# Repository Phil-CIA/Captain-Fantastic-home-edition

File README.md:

# Captain Fantastic – Home Edition

Firmware and hardware files for a restored Captain Fantastic pinball machine running on ESP32.

## Repository Layout

| Path | Description |
|------|-------------|
| `src/` `include/` `data/` | **Legacy firmware** – working single-board ESP32 firmware with External Flash OTA |
| `Captain-v2/` | **Captain v2 firmware** – clean split-MPU architecture (control + matrix boards) |
| `hardware/` | KiCad schematics, gerbers, and board-design backups |
| `docs/` | Project documentation, setup guides, and handoff notes |
| `archive/` | Historical backups, experiments, and recovery copies |
| `music/` | Test audio files used with the music streaming server |

## PlatformIO Projects

This repo contains **multiple PlatformIO projects**:

### 1. Legacy Firmware (root)
- `platformio.ini` at the repository root
- Active environment: `combined_rtos`
- Targets a single ESP32 running gameplay, displays, sound, and OTA

### 2. Captain v2 shared source tree
- `Captain-v2/platformio.ini`
- Shared build definitions and source for split-MPU firmware
- Includes environments for control, matrix, and display-link variants
- Shared source only; not the current matrix bring-up source of truth
- Separates control logic and switch/lamp matrix scanning across two ESP32 boards

### 3. Captain v2 board-specific projects
- `Captain-v2-control/platformio.ini` (control board focused project)
- `Captain-v2-matrix/platformio.ini` (matrix board focused project)
- Both reference shared source under `Captain-v2/` and keep board workflows isolated
- Current active board workflows:
	- Matrix board: `Captain-v2-matrix`, env `captain_matrix_idf`, COM4
	- Control board: `Captain-v2`, env `captain_control`, COM5

> **VS Code tip:** Open the specific project folder you are actively working on (`Captain-v2-control/` or `Captain-v2-matrix/`) so tasks and upload settings stay board-specific.

## Current Development Focus

- Active matrix bring-up/runtime source of truth is `Captain-v2-matrix/src/matrix_app_main.cpp`
- Matrix MCU appears on I2C as a register-based peripheral at `0x24` (HT16K33-style model)
- Matrix/control communication path is now usable for gameplay bring-up:
	- control-side polarity normalization and stability filtering restored usable switch behavior
	- repeated held-switch scoring was fixed
	- gameplay-side bumper / slingshot output mapping has been corrected
- Matrix protocol details and test workflow are documented in:
	- `Captain-v2-matrix/README.md`
- Remaining open issue is residual lamp flicker, but the structured blink component was traced to matrix-side periodic debug / housekeeping work in the refresh loop
- Current stop-point is good enough to continue gameplay bring-up while leaving a later focused flicker cleanup pass
- Hardware iteration note (March 2026): reduce the high-side rail voltage first to improve BSS84/BSS138 gate-drive margin before pursuing transistor substitutions (documented in `Captain-v2-matrix/README.md`, section 11)
- Redesign parking lot for next board iteration: `docs/NEXT_ITERATION_RECOMMENDATIONS.md`

## Music Streaming Server

`music_server.py` / `Start-MusicServer.ps1` stream audio to the pinball machine over Wi-Fi. See `docs/MP3_MUSIC_SETUP.md` and `docs/WIFI_STREAMING_SETUP.md` for setup.

## Documentation

All setup guides and reference docs are in `docs/`. See `docs/REPO_INDEX.md` for a full index.

## KiCad Current Project Entry Points

If KiCad is opening the wrong local copy, use only these repo project files:

- `hardware/kicad/captain_matrix/Pinball matrix board.kicad_pro`
- `hardware/kicad/captain_control/Pinball Control board.kicad_pro`
- `hardware/kicad/legacy/Hat board.kicad_pro` (historical reference project)

To keep KiCad focused on repo paths:

1. Launch with `Open-KiCad.ps1` from repo root.
2. Run `Reset-KiCad-Recents-ToRepo.ps1` once to clear stale KiCad recent/open project paths.
3. Use `hardware/kicad/SOURCE_OF_TRUTH.md` as the canonical board-path map.

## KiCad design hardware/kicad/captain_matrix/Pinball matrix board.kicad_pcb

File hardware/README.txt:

This folder contains hardware design files, schematics, PCB layouts, and fabrication exports for Captain Fantastic v2.

Canonical project map and opening policy:
- kicad/SOURCE_OF_TRUTH.md

## Current Active Designs (v2 split-MPU architecture)

Structure:
- kicad/captain_control/: Main control board (ESP32 DevKit) — gameplay, audio, solenoids, headbox lamps, OTA
- kicad/captain_matrix/: Switch/lamp matrix board (ESP32 DevKit) — playfield matrix scanning, I2C slave
- kicad/7seg_display/: Standalone 7-segment display board (I2C HT16K33, 6-digit)

## Project support files
- kicad/libs/: project symbol/footprint libraries and KiCad tables

## Historical / Legacy
- kicad/legacy/: Hat board (superseded single-board v1 design — trace size and SR enable fixed in v2 split)
- kicad/esp32vroom/: Original ESP32Vroom KiCad project files (historical reference)

Important:
- Open active projects only from kicad/captain_control and kicad/captain_matrix.
- Treat kicad/legacy, kicad/esp32vroom, and archive/ as read-only historical sources.

## Fabrication archives
- gerbers/root-export-esp32vroom/: root-level export set moved from repo root
- gerbers/legacy-gerber-files/: older export set moved from "Gerber files"
- backups/esp32vroom-backups/: historical zipped hardware backups

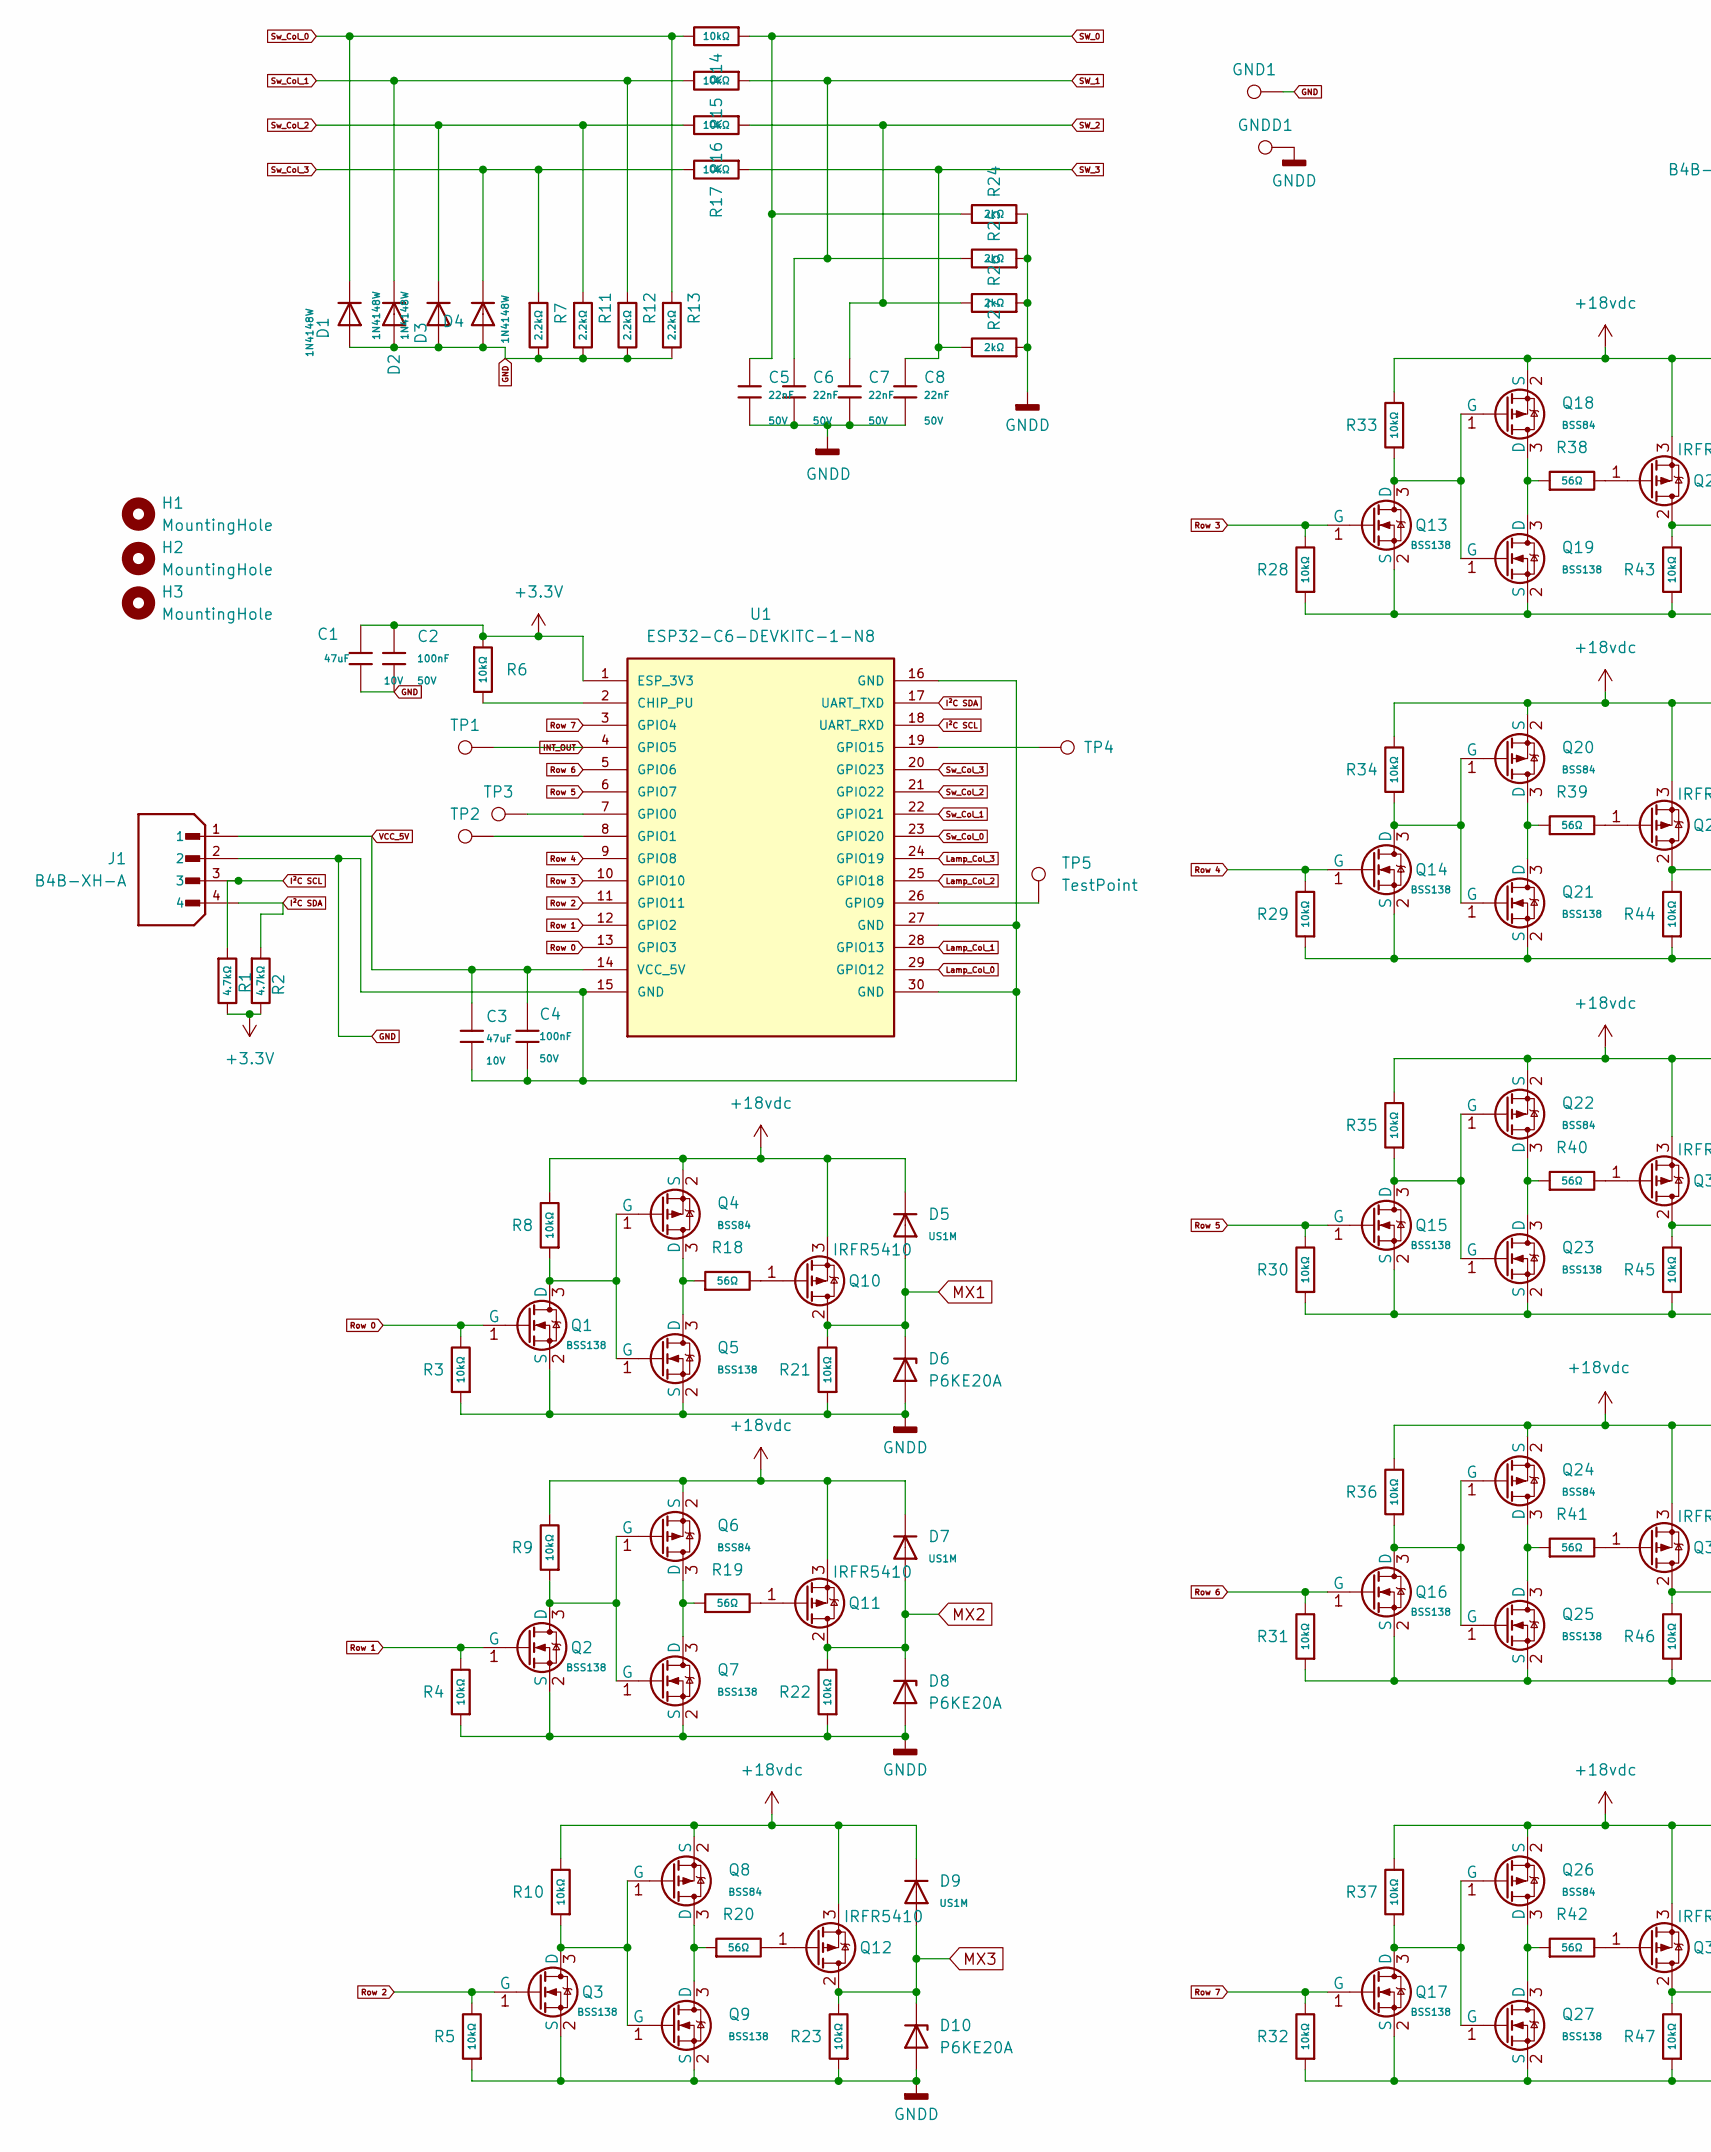
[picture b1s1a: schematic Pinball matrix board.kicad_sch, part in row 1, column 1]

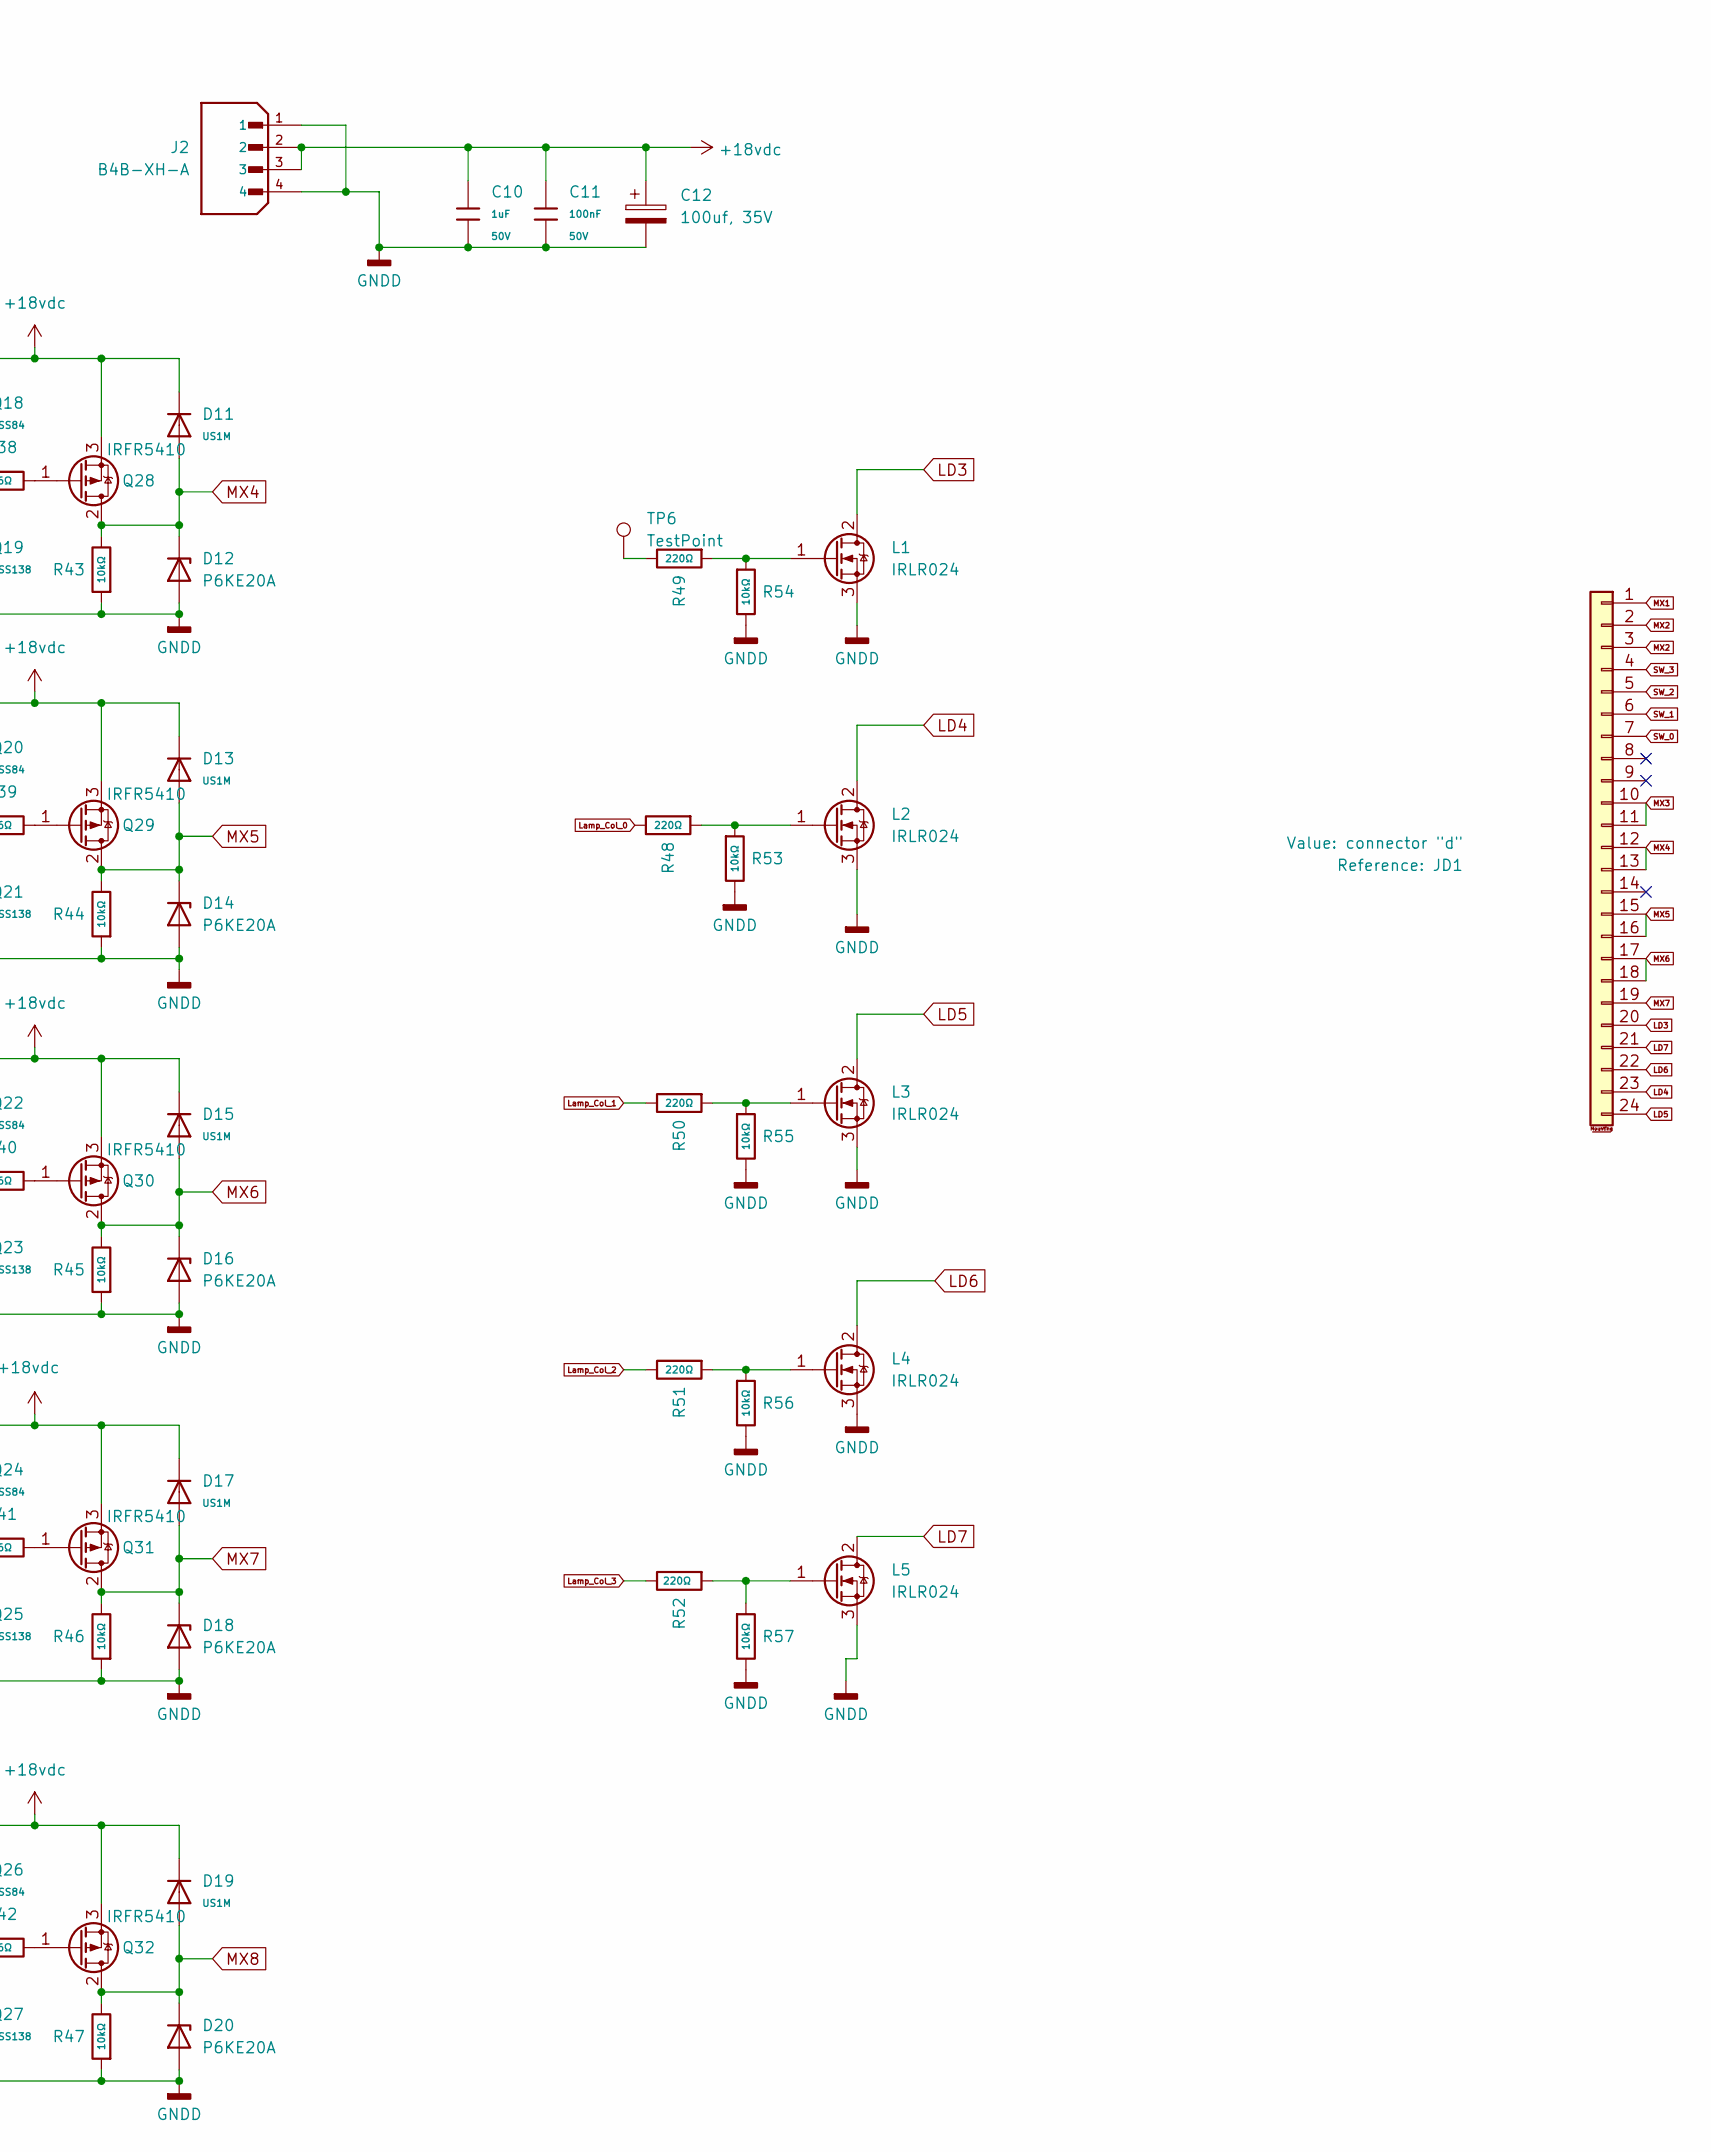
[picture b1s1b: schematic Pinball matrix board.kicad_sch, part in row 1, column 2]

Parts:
C1, C3: 47uF; C_1206; Voltage Rated 10V; Tolerance ±20%; Part CL31A476MPHNNNE; LCSC C96123
C2, C4, C11: 100nF; C_0805; Voltage Rated 50V; Tolerance ±10%; Part CC0805KRX7R9BB104; LCSC C49678
C5, C6, C7, C8: 22nF; C_0805; Voltage Rated 50V; Tolerance ±10%; Part CL21B223KBANNNC; LCSC C1729
C10: 1uF; C_0805; Voltage Rated 50V; Tolerance ±10%; Part CL21B105KBFNNNE; LCSC C28323
C12: 100uf, 35V; CP_Radial_D6.3mm_P2.50mm; LCSC C122240
D1, D2, D3, D4: 1N4148W; D_SOD-123; Forward Voltage (Vf@If) 1V@50mA; Reverse Voltage (Vr) 75V; Part 1N4148W; LCSC C81598
D5, D7, D9, D11, D13, D15, D17, D19: US1M; D_SMA; Forward Voltage (Vf@If) 1.65V@1A; Reverse Voltage (Vr) 1kV; Part US1M; LCSC C412437
D6, D8, D10, D12, D14, D16, D18, D20: P6KE20A; D_SMC; Part SMCJ20CA; LCSC C41411754
GND1: GND; PinSocket_1x01_P2.54mm_Vertical
GNDD1: TestPoint; PinSocket_1x01_P2.54mm_Vertical
H1, H2, H3: MountingHole; MountingHole_3.5mm_Pad
J1, J2: B4B-XH-A; JST_EH_B4B-EH-A_1x04_P2.50mm_Vertical; PARTREV 7/4/21
JD1: connector "d"; Molex_KK-396_5273-12A_1x12_P3.96mm_Vertical
L1: IRLR024; TO-252-2; Manufacturer_Part_Number IRLZ44NPBF; LCSC C3007
L2, L3, L4, L5: IRLR024; TO-252-2; Mouser Part Number 942-IRLZ44NPBF
Q1, Q2, Q3, Q5, Q7, Q9, Q13, Q14, Q15, Q16, Q17, Q19, Q21, Q23, Q25, Q27: BSS138; Q_SOT-23; Part BSS138; LCSC C7420339
Q4, Q6, Q8, Q18, Q20, Q22, Q24, Q26: BSS84; Q_SOT-23; Part BSS84; LCSC C7420340
Q10, Q11, Q12, Q28, Q29, Q30, Q31, Q32: IRFR5410; TO-252-2; Manufacturer_Part_Number IRFR5410TRPBF; LCSC C3018
R1, R2: 4.7kΩ; R_0805; Overload Voltage (Max) 150V; Tolerance ±1%; Part 0805W8F4701T5E; LCSC C17673
R3, R4, R5, R6, R8, R9, R10, R14, R15, R16, R17, R21, R22, R23, R28, R29, R30, R31, R32, R33, R34, R35, R36, R37, R43, R44, R45, R46, R47, R53, R54, R55, R56, R57: 10kΩ; R_0805; Overload Voltage (Max) 150V; Tolerance ±1%; Part 0805W8F1002T5E; LCSC C17414
R7, R11, R12, R13: 2.2kΩ; R_0805; Overload Voltage (Max) 150V; Tolerance ±1%; Part 0805W8F2201T5E; LCSC C17520
R18, R19, R20, R38, R39, R40, R41, R42: 56Ω; R_0805; Overload Voltage (Max) 150V; Tolerance ±1%; Part 0805W8F560JT5E; LCSC C17757
R24, R25, R26, R27: 2kΩ; R_0805; Overload Voltage (Max) 150V; Tolerance ±1%; Part 0805W8F2001T5E; LCSC C17604
R48, R49, R50, R51, R52: 220Ω; R_0805; Overload Voltage (Max) 150V; Tolerance ±1%; Part 0805W8F2200T5E; LCSC C17557
TP1, TP2, TP3, TP4, TP5, TP6: TestPoint; PinSocket_1x01_P2.54mm_Vertical
U1: ESP32-C6-DEVKITC-1-N8; ESP32-C3-DevKitM-1; PARTREV 1.3

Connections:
+3.3V: C1.1, C2.1, R1.2, R2.2, R6.1, U1.1 (ESP_3V3)
+18vdc: C10.1, C11.1, C12.1, D5.1, D7.1, D9.1, D11.1, D13.1, D15.1, D17.1, D19.1, J2.2, J2.3, Q4.2 (S), Q6.2 (S), Q8.2 (S), Q10.3 (S), Q11.3 (S), Q12.3 (S), Q18.2 (S), Q20.2 (S), Q22.2 (S), Q24.2 (S), Q26.2 (S), Q28.3 (S), Q29.3 (S), Q30.3 (S), Q31.3 (S), Q32.3 (S), R8.2, R9.2, R10.2, R33.2, R34.2, R35.2, R36.2, R37.2
GND: C1.2, C2.2, C3.2, C4.2, D1.2, D2.2, D3.2, D4.2, GND1.1, J1.2, R7.2, R11.2, R12.2, R13.2, U1.15 (GND), U1.16 (GND), U1.27 (GND), U1.30 (GND)
GNDD: C5.2, C6.2, C7.2, C8.2, C10.2, C11.2, C12.2, D6.2 (A), D8.2 (A), D10.2 (A), D12.2 (A), D14.2 (A), D16.2 (A), D18.2 (A), D20.2 (A), GNDD1.1, J2.1, J2.4, L1.3 (S), L2.3 (S), L3.3 (S), L4.3 (S), L5.3 (S), Q1.2 (S), Q2.2 (S), Q3.2 (S), Q5.2 (S), Q7.2 (S), Q9.2 (S), Q13.2 (S), Q14.2 (S), Q15.2 (S), Q16.2 (S), Q17.2 (S), Q19.2 (S), Q21.2 (S), Q23.2 (S), Q25.2 (S), Q27.2 (S), R3.1, R4.1, R5.1, R21.1, R22.1, R23.1, R24.1, R25.1, R26.1, R27.1, R28.1, R29.1, R30.1, R31.1, R32.1, R43.1, R44.1, R45.1, R46.1, R47.1, R53.2, R54.2, R55.2, R56.2, R57.2
INT_OUT: TP1.1, U1.4 (GPIO5)
I²C SCL: J1.3, R1.1, U1.18 (UART_RXD)
I²C SDA: J1.4, R2.1, U1.17 (UART_TXD)
LD3: JD1.20, L1.2 (D)
LD4: JD1.23, L2.2 (D)
LD5: JD1.24, L3.2 (D)
LD6: JD1.22, L4.2 (D)
LD7: JD1.21, L5.2 (D)
Lamp_Col_0: R48.2, U1.29 (GPIO12)
Lamp_Col_1: R50.2, U1.28 (GPIO13)
Lamp_Col_2: R51.2, U1.25 (GPIO18)
Lamp_Col_3: R52.2, U1.24 (GPIO19)
MX1: D5.2, D6.1 (K), JD1.1, Q10.2 (D), R21.2
MX2: D7.2, D8.1 (K), JD1.2, JD1.3, Q11.2 (D), R22.2
MX3: D9.2, D10.1 (K), JD1.10, JD1.11, Q12.2 (D), R23.2
MX4: D11.2, D12.1 (K), JD1.12, JD1.13, Q28.2 (D), R43.2
MX5: D13.2, D14.1 (K), JD1.15, JD1.16, Q29.2 (D), R44.2
MX6: D15.2, D16.1 (K), JD1.17, JD1.18, Q30.2 (D), R45.2
MX7: D17.2, D18.1 (K), JD1.19, Q31.2 (D), R46.2
MX8: D19.2, D20.1 (K), Q32.2 (D), R47.2
unnamed: L1.1 (G), R49.1, R54.1
unnamed: L2.1 (G), R48.1, R53.1
unnamed: L3.1 (G), R50.1, R55.1
unnamed: L4.1 (G), R51.1, R56.1
unnamed: L5.1 (G), R52.1, R57.1
unnamed: Q1.3 (D), Q4.1 (G), Q5.1 (G), R8.1
unnamed: Q2.3 (D), Q6.1 (G), Q7.1 (G), R9.1
unnamed: Q3.3 (D), Q8.1 (G), Q9.1 (G), R10.1
unnamed: Q4.3 (D), Q5.3 (D), R18.1
unnamed: Q6.3 (D), Q7.3 (D), R19.1
unnamed: Q8.3 (D), Q9.3 (D), R20.1
unnamed: Q10.1 (G), R18.2
unnamed: Q11.1 (G), R19.2
unnamed: Q12.1 (G), R20.2
unnamed: Q13.3 (D), Q18.1 (G), Q19.1 (G), R33.1
unnamed: Q14.3 (D), Q20.1 (G), Q21.1 (G), R34.1
unnamed: Q15.3 (D), Q22.1 (G), Q23.1 (G), R35.1
unnamed: Q16.3 (D), Q24.1 (G), Q25.1 (G), R36.1
unnamed: Q17.3 (D), Q26.1 (G), Q27.1 (G), R37.1
unnamed: Q18.3 (D), Q19.3 (D), R38.1
unnamed: Q20.3 (D), Q21.3 (D), R39.1
unnamed: Q22.3 (D), Q23.3 (D), R40.1
unnamed: Q24.3 (D), Q25.3 (D), R41.1
unnamed: Q26.3 (D), Q27.3 (D), R42.1
unnamed: Q28.1 (G), R38.2
unnamed: Q29.1 (G), R39.2
unnamed: Q30.1 (G), R40.2
unnamed: Q31.1 (G), R41.2
unnamed: Q32.1 (G), R42.2
unnamed: R49.2, TP6.1
unnamed: R6.2, U1.2 (CHIP_PU)
unnamed: TP3.1, U1.7 (GPIO0)
unnamed: TP2.1, U1.8 (GPIO1)
unnamed: TP5.1, U1.26 (GPIO9)
unnamed: TP4.1, U1.19 (GPIO15)
Row 0: Q1.1 (G), R3.2, U1.13 (GPIO3)
Row 1: Q2.1 (G), R4.2, U1.12 (GPIO2)
Row 2: Q3.1 (G), R5.2, U1.11 (GPIO11)
Row 3: Q13.1 (G), R28.2, U1.10 (GPIO10)
Row 4: Q14.1 (G), R29.2, U1.9 (GPIO8)
Row 5: Q15.1 (G), R30.2, U1.6 (GPIO7)
Row 6: Q16.1 (G), R31.2, U1.5 (GPIO6)
Row 7: Q17.1 (G), R32.2, U1.3 (GPIO4)
SW_0: C5.1, JD1.7, R14.1, R24.2
SW_1: C6.1, JD1.6, R15.1, R25.2
SW_2: C7.1, JD1.5, R16.1, R26.2
SW_3: C8.1, JD1.4, R17.1, R27.2
Sw_Col_0: D1.1, R13.1, R14.2, U1.23 (GPIO20)
Sw_Col_1: D2.1, R12.1, R15.2, U1.22 (GPIO21)
Sw_Col_2: D3.1, R11.1, R16.2, U1.21 (GPIO22)
Sw_Col_3: D4.1, R7.1, R17.2, U1.20 (GPIO23)
VCC_5V: C3.1, C4.1, J1.1, U1.14 (VCC_5V)

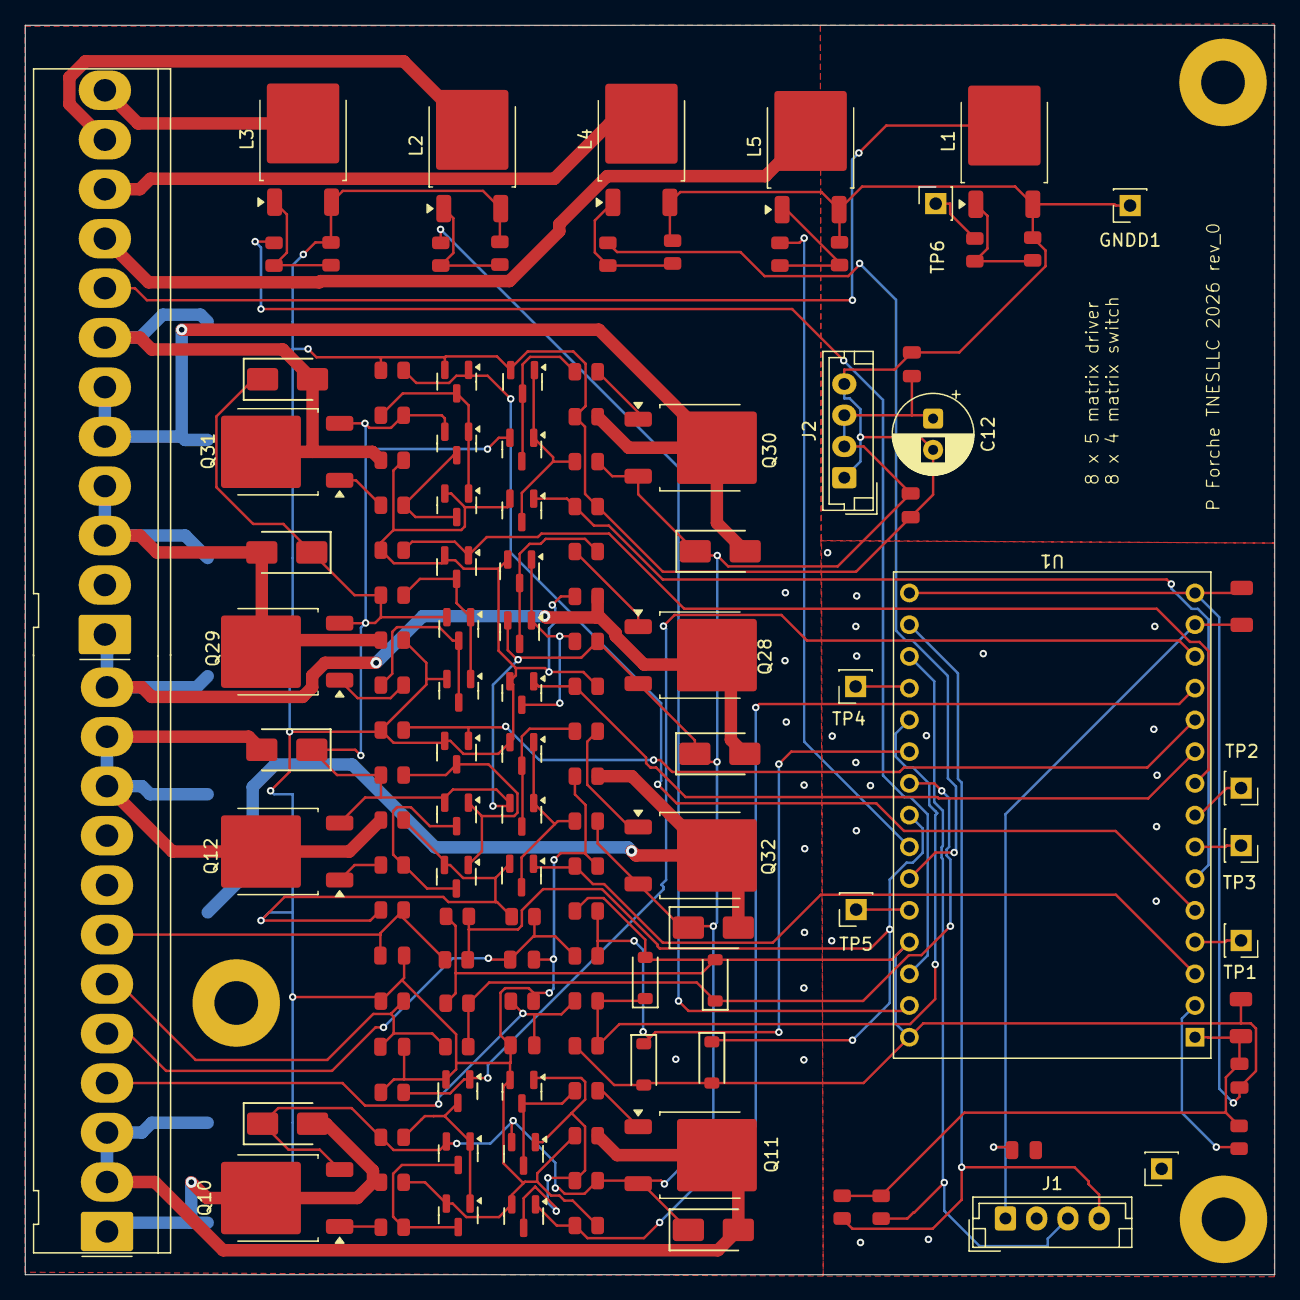
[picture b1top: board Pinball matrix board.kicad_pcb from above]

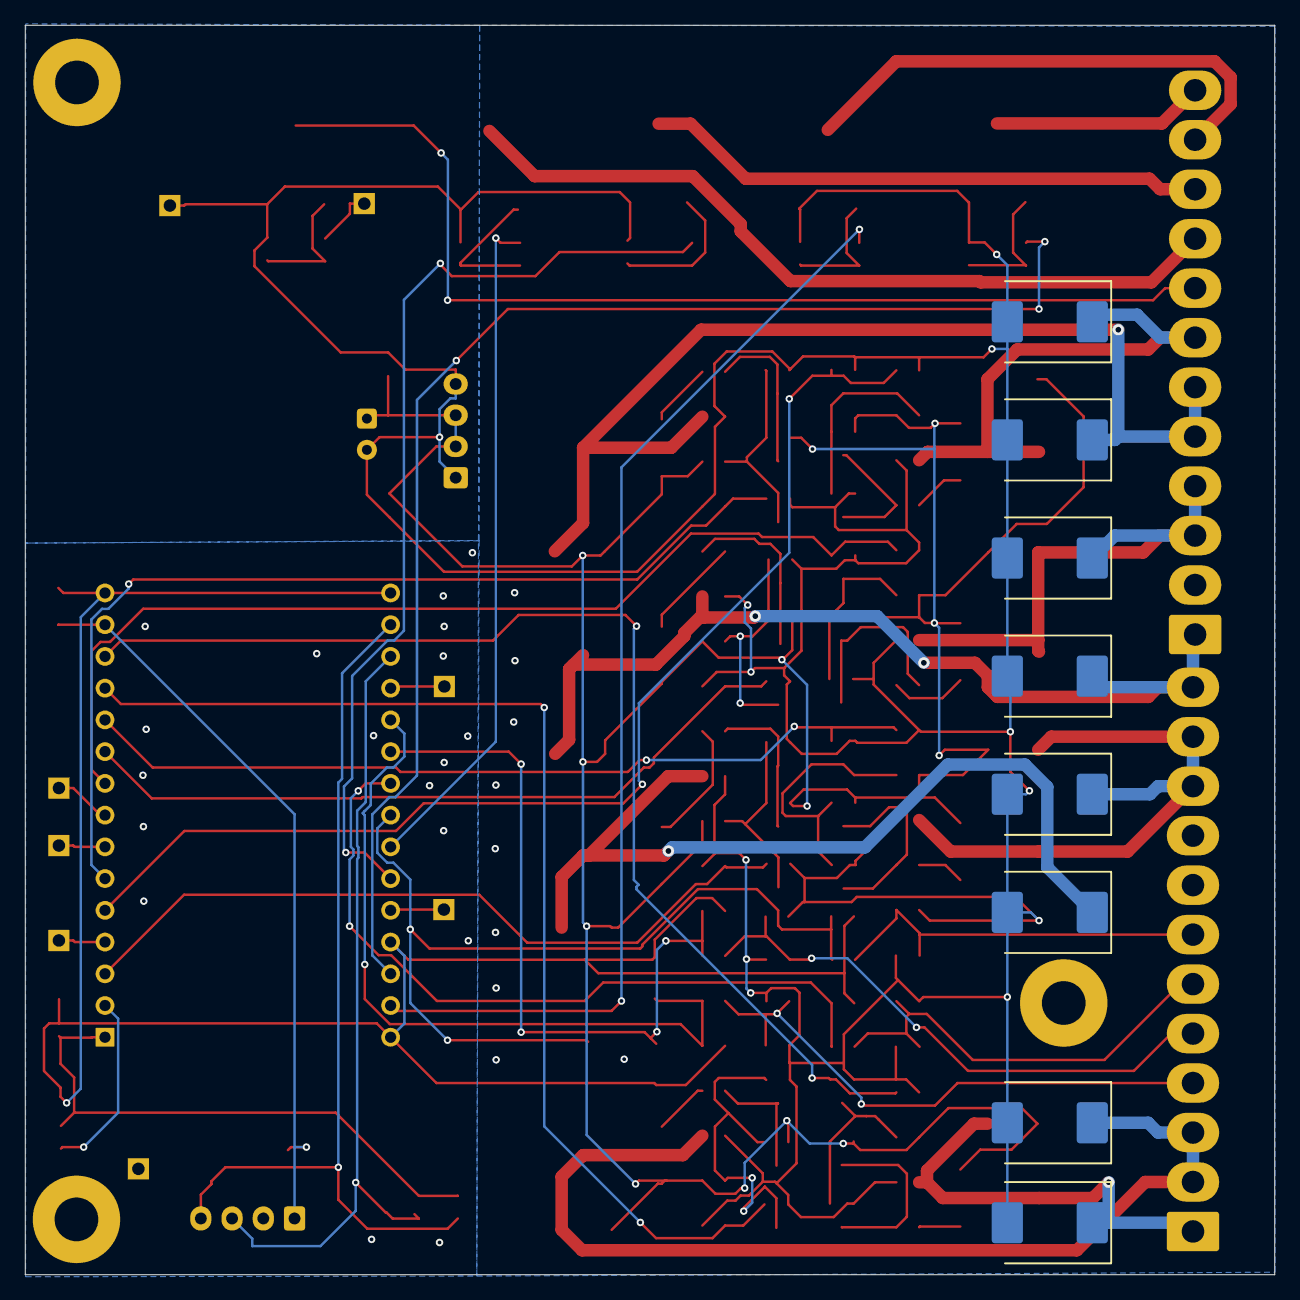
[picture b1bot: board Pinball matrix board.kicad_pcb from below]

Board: 2 copper layers, 100.0 x 100.0 mm, 140 parts (8 on the bottom side), 76 nets.
